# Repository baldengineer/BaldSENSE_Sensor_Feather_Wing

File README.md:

## BaldSense Sensor Feather Wing
Project to fit a temperature, humidity, light, and sound sensor to an Adafruit Feather wing form factor.

Minimal environmental sensor board for characterizing a specific location. 

## Sensors Included:
- **Temp / Humidity**: 
    - SHT30-DIS-B2.5KS
- **Light**: 
    - APDS9960
- **Sound (Mic)**: 
    - MP34DT01TR-M
- **Real-Time Clock (RTC)**: 
    - DS3231S

## Status: Work In Progress
Originally created as a livestream project. Being updated for a long-term IoT project. 

V3 board fixes many issues with v1 and v2. Testing is underway with a [FeatherS3 board](https://unexpectedmaker.com/shop.html#!/FeatherS3/p/577111310/category=0) provided by [Unexpected Maker](https://unexpectedmaker.com). 

So far, each sensor is working as expected.

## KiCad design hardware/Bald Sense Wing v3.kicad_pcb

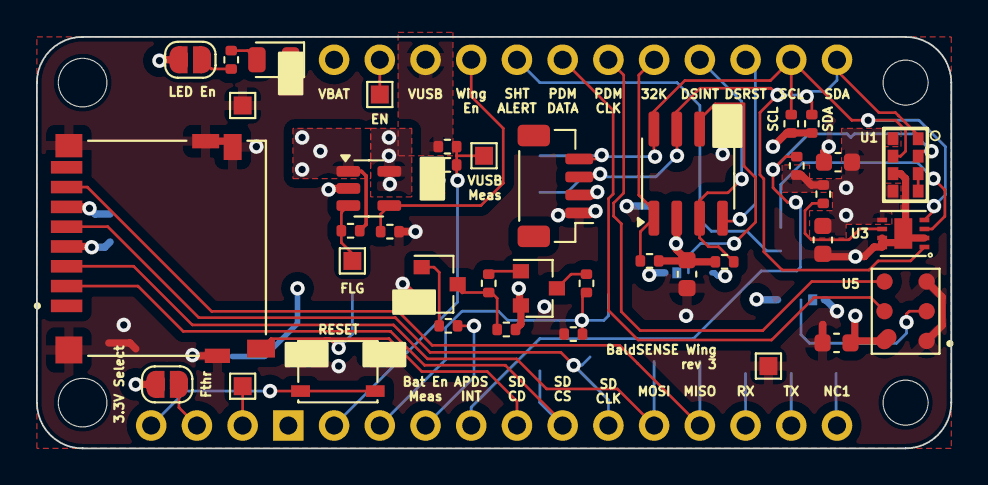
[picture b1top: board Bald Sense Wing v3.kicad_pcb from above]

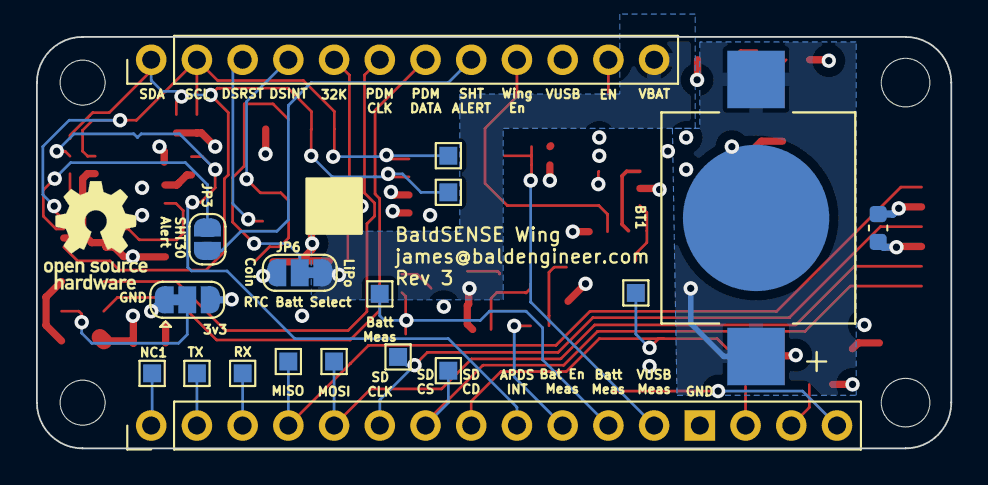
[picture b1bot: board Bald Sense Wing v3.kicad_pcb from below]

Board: 4 copper layers, 50.8 x 22.9 mm, 58 parts (19 on the bottom side), 42 nets.

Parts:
BT1: 10mm; MPD_BK-870
C1, C2, C3, C4, C7: 1uF; C_0603_1608Metric
D1: PWR_LED; LED_0805_2012Metric
J1: feather long; PinHeader_1x16_P2.54mm_Vertical
J2: feather short; PinHeader_1x12_P2.54mm_Vertical
J3: 1140084168; AMPHENOL_1140084168
J4: JST_SH_BM04B-SRSS-TB; JST_SH_BM04B-SRSS-TB_1x04-1MP_P1.00mm_Vertical
JP1: 3.3V Select; SolderJumper-2_P1.3mm_Open_RoundedPad1.0x1.5mm
JP2, JP6: RTC Batt Select; SolderJumper-3_P1.3mm_Bridged12_RoundedPad1.0x1.5mm
JP3: SHT30-Alert; SolderJumper-2_P1.3mm_Open_RoundedPad1.0x1.5mm
JP5: LED En; SolderJumper-2_P1.3mm_Open_RoundedPad1.0x1.5mm
Q1: Q_PNP_BEC; SOT-23
Q2: Q_NPN_BEC; SOT-23
R1, R2, R3, R4, R5, R6, R7, R10, R12, R13, R14, R15, R16: 10K; R_0402_1005Metric
R8, R9, R11: 1K; R_0402_1005Metric
SW1: PTS810SJK250SMTR LFS; SW_SPST_PTS810
TP1, TP2, TP3, TP4, TP5, TP6, TP8, TP9, TP10, TP11, TP12, TP13, TP14, TP15, TP16, TP17, TP18: Test Point; TestPoint_Pad_1.0x1.0mm
TP7: FLG; TestPoint_Pad_1.0x1.0mm
U1: APDS-9960
U2: DS3231MZ; SOIC-8_3.9x4.9mm_P1.27mm
U3: SHT30-DIS; DFN250X250X100-9N
U4: AP2151AW-7; SOT-23-5
U5: CMM-4737DT-26186-TR; XDCR_CMM-4737DT-26186-TR

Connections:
+3.3V: C1.1, C2.1, C3.1, C4.1, C7.1, J3.4 (Vdd), J4.2, JP1.1 (A), JP2.3 (B), JP5.1 (A), R1.1, R2.1, R3.2, R12.1, R13.1, R15.2, R16.2, U1.5 (LEDA), U1.8 (VDD), U2.2 (VCC), U3.5 (VDD), U4.1 (OUT), U5.6 (VDD)
+3v3_Feather: J1.15, JP1.2 (B), U4.5 (IN)
+RTC_BATT: BT1.1 (+), JP6.3 (B)
+V_RTC: JP6.2 (C), U2.6 (VBAT)
+Vbatt: J2.12, JP6.1 (A), Q1.2 (E), R7.2
+Vusb: J2.10, R5.1
/32KHz: J2.5, R1.2, U2.1 (32KHZ)
/APDS_INT: J1.9, R16.1, U1.2 (INT)
/Batt_Meas: J1.11, R10.1, R14.2, TP5.1
/Batt_Meas_En: J1.10, R9.2
/DS3231_INT: J2.4, R2.2, U2.3 (~INT/SQW)
/DS3231_RST: J2.3, U2.4 (~RST)
/EN: J2.11, TP8.1
/Load_SW_En: J2.9, R4.2, U4.4 (EN)
/NC1: J1.1, TP4.1
/NC2: J1.14, TP1.1
/PDM_CLK: J2.6, U5.4 (CLOCK)
/PDM_DATA: J2.7, U5.5 (DATA)
/RX: J1.3, TP2.1
/SCL: J2.2, J4.4, R13.2, TP9.1, U1.7 (SCL), U2.8 (SCL), U3.4 (SCL)
/SDA: J2.1, J4.3, R12.2, TP10.1, U1.1 (SDA), U2.7 (SDA), U3.1 (SDA)
/SD_CD: J1.8, J3.9 (CD_SW1), TP15.1
/SD_CLK: J1.6, J3.5 (CLOCK), TP13.1
/SD_CS: J1.7, J3.2 (CD/DATA_BIT_3), TP14.1
/SD_DIn: J1.5, J3.3 (CMD/RESP), TP12.1
/SD_DOut: J1.4, J3.7 (DATA_BIT_0), TP11.1
/SHT30_ALERT: J2.8, JP3.2 (B)
/TX: J1.2, TP3.1
/VUSB_Meas: J1.12, R5.2, R6.1, TP6.1
/~RST: J1.16, SW1.2 (B)
GND: BT1.2 (-), C1.2, C2.2, C3.2, C4.2, C7.2, D1.1 (K), J1.13, J3.6 (Vss), J3.10 (CD_SW2), J3.S1 (SHIELD), J3.S2 (SHIELD), J3.S3 (SHIELD), J3.S4 (SHIELD), J4.1, JP2.1 (A), Q2.2 (E), R4.1, R6.2, R14.1, SW1.1 (A), TP16.1, TP17.1, TP18.1, U1.6 (GND), U2.5 (GND), U3.2 (ADDR), U3.7 (R), U3.8 (VSS), U3.9 (EXP), U4.2 (GND), U5.1 (GND), U5.3 (GND)
unnamed: D1.2 (A), R11.1
unnamed: JP2.2 (C), U5.2 (L/R)
unnamed: JP3.1 (A), U3.3 (ALERT)
unnamed: JP5.2 (B), R11.2
unnamed: Q1.1 (B), R8.2
unnamed: Q1.3 (C), R10.2
unnamed: Q2.1 (B), R9.1
unnamed: Q2.3 (C), R7.1, R8.1
unnamed: U1.3 (LDR), U1.4 (LEDK)
unnamed: R3.1, U3.6 (~RESET)
unnamed: R15.1, TP7.1, U4.3 (FLG)

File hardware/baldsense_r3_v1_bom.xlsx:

Designator | Value | Footprint | Populate | MPN | Manufacturer | MPN | Manufacturer
BT1 | 10mm | MPD_BK-870 | 0
C1 | 1uF | C_0603_1608Metric | 1 | LMK107B7105KAHT | Taiyo Yuden | MF-CAP-0805-1uF | MacroFab
C2 | 1uF | C_0603_1608Metric | 1 | LMK107B7105KAHT | Taiyo Yuden | MF-CAP-0805-1uF | MacroFab
C3 | 1uF | C_0603_1608Metric | 1 | LMK107B7105KAHT | Taiyo Yuden | MF-CAP-0805-1uF | MacroFab
C4 | 1uF | C_0603_1608Metric | 1 | LMK107B7105KAHT | Taiyo Yuden | MF-CAP-0805-1uF | MacroFab
C7 | 1uF | C_0603_1608Metric | 0 | LMK107B7105KAHT | Taiyo Yuden | MF-CAP-0805-1uF | MacroFab
D1 | PWR_LED | LED_0805_2012Metric | 1 | MF-LED-0805-GREEN | MacroFab
J1 | feather long | PinHeader_1x16_P2.54mm_Vertical | 0
J2 | feather short | PinHeader_1x12_P2.54mm_Vertical | 0
J3 | 1140084168 | AMPHENOL_1140084168 | 1 | 1140084168 | Amphenol
J4 | STEMMA-QT | JST_SH_BM04B-SRSS-TB_1x04-1MP_P1.00mm_Vertical | 0
JP1 | 3.3V | SolderJumper-2_P1.3mm_Open_RoundedPad1.0x1.5mm | 0
JP2 | RTC Batt Select | SolderJumper-3_P1.3mm_Bridged12_RoundedPad1.0x1.5mm | 0
JP3 | SHT30-Alert | SolderJumper-2_P1.3mm_Open_RoundedPad1.0x1.5mm | 0
JP5 | LED En | SolderJumper-2_P1.3mm_Open_RoundedPad1.0x1.5mm | 0
JP6 | RTC Batt Select | SolderJumper-3_P1.3mm_Bridged12_RoundedPad1.0x1.5mm | 0
Q1 | Q_PNP_BEC | SOT-23 | 1 | MMBT3906LT3G | onsemi | MF-DSC-SOT233-MMBT3906 | MacroFab
Q2 | Q_NPN_BEC | SOT-23 | 1 | MMBT3904LT3G | onsemi | MF-DSC-SOT233-MMBT3904 | MacroFab
R1 | 10K | R_0402_1005Metric | 1 | MF-RES-0402-10K | MacroFab
R10 | 10K | R_0402_1005Metric | 1 | MF-RES-0402-10K | MacroFab
R11 | 1K | R_0402_1005Metric | 1 | MF-RES-0402-1K | MacroFab
R12 | 10K | R_0402_1005Metric | 1 | MF-RES-0402-10K | MacroFab
R13 | 10K | R_0402_1005Metric | 1 | MF-RES-0402-10K | MacroFab
R14 | 10K | R_0402_1005Metric | 1 | MF-RES-0402-10K | MacroFab
R15 | 10K | R_0402_1005Metric | 0 | MF-RES-0402-10K | MacroFab
R16 | 10K | R_0402_1005Metric | 1 | MF-RES-0402-10K | MacroFab
R2 | 10K | R_0402_1005Metric | 1 | MF-RES-0402-10K | MacroFab
R3 | 10K | R_0402_1005Metric | 1 | MF-RES-0402-10K | MacroFab
R4 | 10K | R_0402_1005Metric | 1 | MF-RES-0402-10K | MacroFab
R5 | 10K | R_0402_1005Metric | 1 | MF-RES-0402-10K | MacroFab
R6 | 10K | R_0402_1005Metric | 1 | MF-RES-0402-10K | MacroFab
R7 | 10K | R_0402_1005Metric | 1 | MF-RES-0402-10K | MacroFab
R8 | 1K | R_0402_1005Metric | 1 | MF-RES-0402-1K | MacroFab
R9 | 1K | R_0402_1005Metric | 1 | MF-RES-0402-1K | MacroFab
SW1 | PTS810 | SW_SPST_PTS810_with_3D | 1 | PTS810SJK250SMTRLFS | C&K Components
TP1 | Test Point | TestPoint_Pad_1.0x1.0mm | 0
TP2 | Test Point | TestPoint_Pad_1.0x1.0mm | 0
TP3 | Test Point | TestPoint_Pad_1.0x1.0mm | 0
TP4 | Test Point | TestPoint_Pad_1.0x1.0mm | 0
TP5 | Test Point | TestPoint_Pad_1.0x1.0mm | 0
TP6 | Test Point | TestPoint_Pad_1.0x1.0mm | 0
TP7 | FLG | TestPoint_Pad_1.0x1.0mm | 0
TP8 | Test Point | TestPoint_Pad_1.0x1.0mm | 0
U1 | APDS-9960 | APDS-9960 | 1 | APDS-9960 | Broadcom
U2 | DS3231MZ | SOIC-8_3.9x4.9mm_P1.27mm | 1 | DS3231MZ | Dallas Semiconductor | DS3231MZ+ | Analog Devices
U3 | SHT30-DIS | DFN250X250X100-9N | 1 | SHT30-DIS | Sensirion | SHT30-DIS-P2.5KS | Sensirion
U4 | AP2151AW-7 | SOT-23-5 | 1 | AP2151AW-7 | Diodes Inc.
U5 | CMM-4737DT-26186-TR | XDCR_CMM-4737DT-26186-TR | 1 | CMM-4737DT-26186-TR | CUI Devices

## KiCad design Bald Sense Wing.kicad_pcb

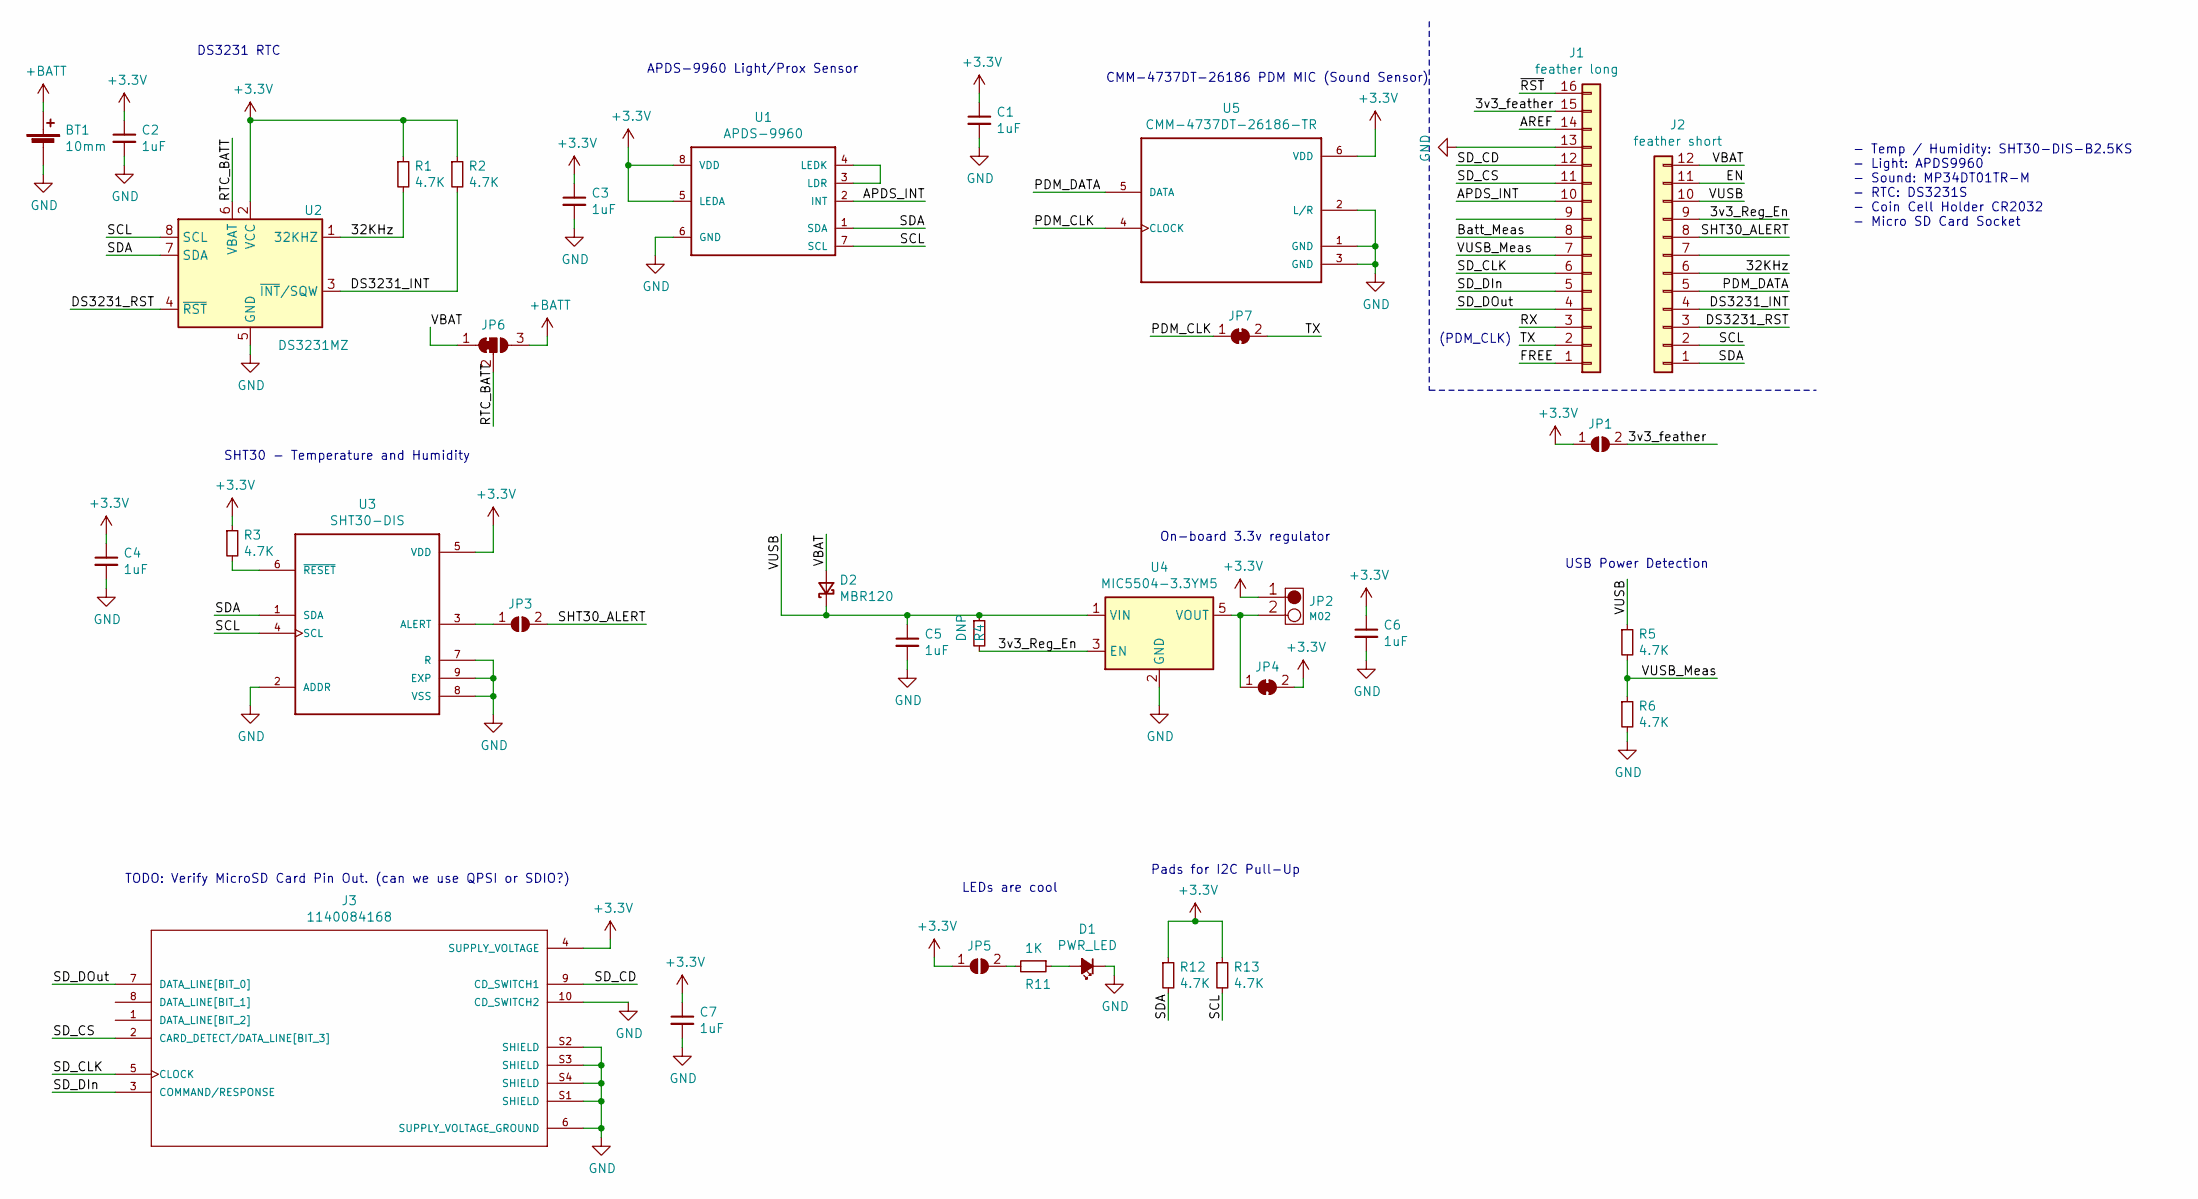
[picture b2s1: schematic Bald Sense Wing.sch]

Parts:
BT1: 10mm; MPD_BK-870
C1, C2, C3, C4, C5, C6, C7: 1uF; C_0805_2012Metric
D1: PWR_LED; LED_1206_3216Metric
D2: MBR120; D_SOD-123F
J1: feather long; PinHeader_1x16_P2.54mm_Vertical
J2: feather short; PinHeader_1x12_P2.54mm_Vertical
J3: 1140084168; AMPHENOL_1140084168
JP1: 3.3V Select; SolderJumper-2_P1.3mm_Open_RoundedPad1.0x1.5mm
JP2: M02; PinHeader_1x02_P2.54mm_Vertical
JP3: SHT30-Alert; SolderJumper-2_P1.3mm_Open_RoundedPad1.0x1.5mm
JP4: Reg En; SolderJumper-2_P1.3mm_Bridged_RoundedPad1.0x1.5mm
JP5: LED En; SolderJumper-2_P1.3mm_Open_RoundedPad1.0x1.5mm
JP6: RTC Batt Select; SolderJumper-3_P1.3mm_Bridged12_RoundedPad1.0x1.5mm
JP7: SolderJumper_2_Bridged; SolderJumper-2_P1.3mm_Bridged_RoundedPad1.0x1.5mm
R1, R2, R3, R5, R6, R12, R13: 4.7K; R_0805_2012Metric
R4: DNP; R_0805_2012Metric
R11: 1K; R_0805_2012Metric
U1: APDS-9960
U2: DS3231MZ; SOIC-8_3.9x4.9mm_P1.27mm
U3: SHT30-DIS; DFN250X250X100-9N
U4: MIC5504-3.3YM5; SOT-23-5
U5: CMM-4737DT-26186-TR; XDCR_CMM-4737DT-26186-TR

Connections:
+3V3: C1.1, C2.1, C3.1, C4.1, C6.1, C7.1, J3.4 (SUPPLY_VOLTAGE), JP1.1 (A), JP2.1, JP4.2 (B), JP5.1 (A), R1.1, R2.1, R3.1, R12.1, R13.1, U1.5 (LEDA), U1.8 (VDD), U2.2 (VCC), U3.5 (VDD), U5.6 (VDD)
+BATT: BT1.1 (+), JP6.3 (B)
/3v3_Reg_En: J2.9, R4.2, U4.3 (EN)
/3v3_feather: J1.15, JP1.2 (B)
/32KHz: J2.6, R1.2, U2.1 (32KHZ)
/APDS_INT: J1.10, U1.2 (INT)
/AREF: J1.14
/Batt_Meas: J1.8
/DS3231_INT: J2.4, R2.2, U2.3 (~INT~/SQW)
/DS3231_RST: J2.3, U2.4 (~RST)
/EN: J2.11
/FREE: J1.1
/PDM_CLK: JP7.1 (A), U5.4 (CLOCK)
/PDM_DATA: J2.5, U5.5 (DATA)
/RTC_BATT: JP6.2 (C), U2.6 (VBAT)
/RX: J1.3
/SCL: J2.2, R13.2, U1.7 (SCL), U2.8 (SCL), U3.4 (SCL)
/SDA: J2.1, R12.2, U1.1 (SDA), U2.7 (SDA), U3.1 (SDA)
/SD_CD: J1.12, J3.9 (CD_SWITCH1)
/SD_CLK: J1.6, J3.5 (CLOCK)
/SD_CS: J1.11, J3.2 (CARD_DETECT/DATA_LINE[BIT_3])
/SD_DIn: J1.5, J3.3 (COMMAND/RESPONSE)
/SD_DOut: J1.4, J3.7 (DATA_LINE[BIT_0])
/SHT30_ALERT: J2.8, JP3.2 (B)
/TX: J1.2, JP7.2 (B)
/VBAT: D2.2 (A), J2.12, JP6.1 (A)
/VUSB: C5.1, D2.1 (K), J2.10, R4.1, R5.1, U4.1 (VIN)
/VUSB_Meas: J1.7, R5.2, R6.1
/~RST: J1.16
GND: BT1.2 (-), C1.2, C2.2, C3.2, C4.2, C5.2, C6.2, C7.2, D1.1 (K), J1.13, J3.6 (SUPPLY_VOLTAGE_GROUND), J3.10 (CD_SWITCH2), J3.S1 (SHIELD), J3.S2 (SHIELD), J3.S3 (SHIELD), J3.S4 (SHIELD), R6.2, U1.6 (GND), U2.5 (GND), U3.2 (ADDR), U3.7 (R), U3.8 (VSS), U3.9 (EXP), U4.2 (GND), U5.1 (GND), U5.2 (L/R), U5.3 (GND)
unnamed: D1.2 (A), R11.1
unnamed: JP2.2, JP4.1 (A), U4.5 (VOUT)
unnamed: JP3.1 (A), U3.3 (ALERT)
unnamed: JP5.2 (B), R11.2
unnamed: R3.2, U3.6 (~RESET~)
unnamed: U1.3 (LDR), U1.4 (LEDK)

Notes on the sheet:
- Temp / Humidity: SHT30-DIS-B2.5KS - Light: APDS9960 - Sound: MP34DT01TR-M - RTC: DS3231S - Coin Cell Holder CR2032 - Micro SD Card Socket
DS3231 RTC
CMM-4737DT-26186 PDM MIC (Sound Sensor)
APDS-9960 Light/Prox Sensor
SHT30 - Temperature and Humidity
TODO: Verify MicroSD Card Pin Out. (can we use QPSI or SDIO?)
USB Power Detection
On-board 3.3v regulator
LEDs are cool
Pads for I2C Pull-Up
(PDM_CLK)

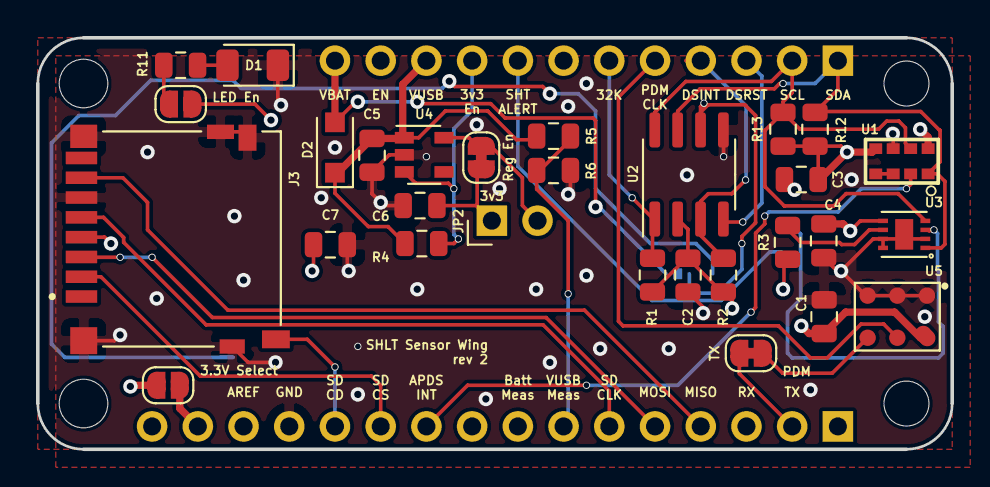
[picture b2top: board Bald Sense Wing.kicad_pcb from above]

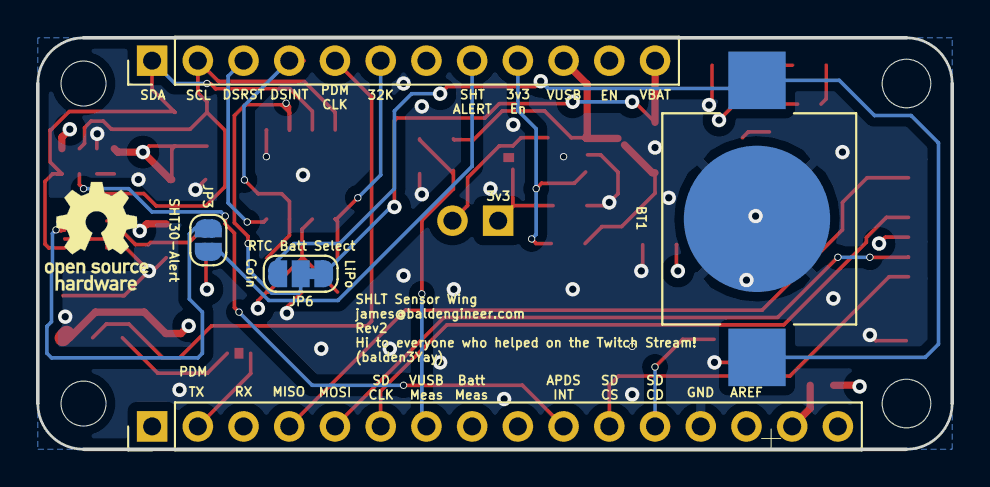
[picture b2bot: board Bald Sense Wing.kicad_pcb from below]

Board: 4 copper layers, 50.8 x 22.9 mm, 34 parts (5 on the bottom side), 30 nets.

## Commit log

2020-05-23 Inital PCB Footprint Placements
    Thank you to everyone in the live stream chat.
2020-05-23 Re-arranged PCB
    Moved SD Card slot to other side and put sensors on an edge.
2020-05-23 Re-arranged PCB parts to a more logical layout
    Switched to SOT-23 3906 because the SO70 looked too small.
    Switched PDM to a Cui CMM-4737DT-26186.
    Fixed two-pin header footprint (was socket before)
    Changed to 10mm battery holder
    Changed Footprint reference sizes
2020-05-24 Minor updates
2020-05-28 Finished v1 layout
    Thanks to everyone on the stream!
2020-05-30 Fixed courtyards and updated silkscreens
2020-06-04 Cleaned up silkscreens and submitted board
2020-07-16 Made changes for v2
    - Fixed power rail problem (diode to VBAT and VUSB).
    - Rotated Light and Sound sensors
    - Removed battery voltage divider circuit
    - Rotated SD Card 180 degrees
    - Re-mapped IO pins to be more compatible with other Feathers
2022-04-20 moved kicad files to separate directory
2022-04-20 adding old arduino project
2022-04-21 added light sensor to m0 code.
2022-05-04 added gitignore
2022-05-04 kicad 6 update
2022-05-04 Sleep and delay changes for wbw video
2024-05-21 unknown changes
2024-05-21 ignorning old kicad temp files
2024-05-21 re-organized files and setup for v3
2024-05-22 readme update
2024-06-15 re-worked pinout to match m0 lora feather
2024-06-15 removed LDO and unconnected a few pins to be compatible with feathers3
2024-06-15 changed R to 0402 and C to 0603
2024-06-20 Cleaned up older custom symbols. Ran track clean-up on PCB.
2024-06-20 updated pin header silk
2024-06-24 added load switch and changed power markers
2024-06-24 re-worked pin assignments of custom packages and passed ERC
2024-06-24 added stemma qt connector
2024-06-25 14 unrouted
2024-06-25 working on voltage rails
2024-06-25 first to 0 unrouted!
2024-06-25 Cleaned up power rails. Prepping for Macrofab DRC
2024-06-25 updated custom footprints with (local) 3d models. ready for fab.
2024-06-25 v3 project render update
2024-06-25 updated pns
2024-06-26 Edge Cut issue with mismatched widths
2024-06-26 cleaned up schematic
2024-06-26 design review changes incorporated
2024-06-26 rev3 v2 fab submit
2024-07-20 sht30 added
2024-07-20 apds9660 added
2024-07-20 tried adding PDM but not supported on esp32 :(
2024-07-20 battery and usb voltage measurements
2024-07-20 removed pdm references while working on rtc
2024-07-20 ds3231 rtc added with support for updating time via serial
2024-07-21 RTC string creation tool (runs on pc)
2024-07-21 sd card detect and write working (initial)
2024-07-21 csv to sd card working
2024-07-21 starting down wifi path
2024-07-21 added wifi and mqtt yay!
2024-07-21 added stop function to prep for deep sleep also added additional information to CSV and MQTT plus a MQTT status to the CSV saving
2024-07-21 deep sleep implemented, now time to test
2024-07-21 added SLEEP_SECONDS and moved to correct director
2024-07-21 README for FS3-CP firmware and updated project readme
2024-07-21 mqtt_logger to capture mqtt messages to a file
2024-07-21 first long-term test attempt, not so great
2024-07-23 what was this file?
2024-07-23 added checks for wifi and mqtt before attempting to use them. moved sleep time and ID to settings.toml to make it easier to deploy to multiple feather stacks.
2024-07-29 STEP export for enclosure
2024-11-30 enclosure
2024-11-30 stls for enclosure
2024-11-30 initial aio code. should probably find a way to support both aio and private mqtt
2024-12-01 cp safemode force reset
2024-12-08 update RTC via NTP when connected to USB
2024-12-08 cleaned up os.env stuff
2024-12-08 added i2c not connected handling
2024-12-08 added option for updating rtc and exception handling
2024-12-08 added WDT and cleaned up env variables (converted from try to check if value is None)
2024-12-08 cutout for USB (won't be sealed but will be protected)
2024-12-08 adds build number, fixes #9
2024-12-08 cp README updates
